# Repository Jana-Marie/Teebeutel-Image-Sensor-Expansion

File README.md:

# Teebeutel Image Sensor Expansion

Upgrade your Teebeutel with different wavelength sensitive parts today!

This addon aims to add minimal thermal vision (GridEye, 8x8px, -20..120°C) to your Teebeutel, as well as an optical camera. However the latter is rather a reverse engineering take on Omnivisions OVM6948 and OV6946 sensors. It also adds a 8x8px ToF camera to your Teebeutel.

Nyaaa~

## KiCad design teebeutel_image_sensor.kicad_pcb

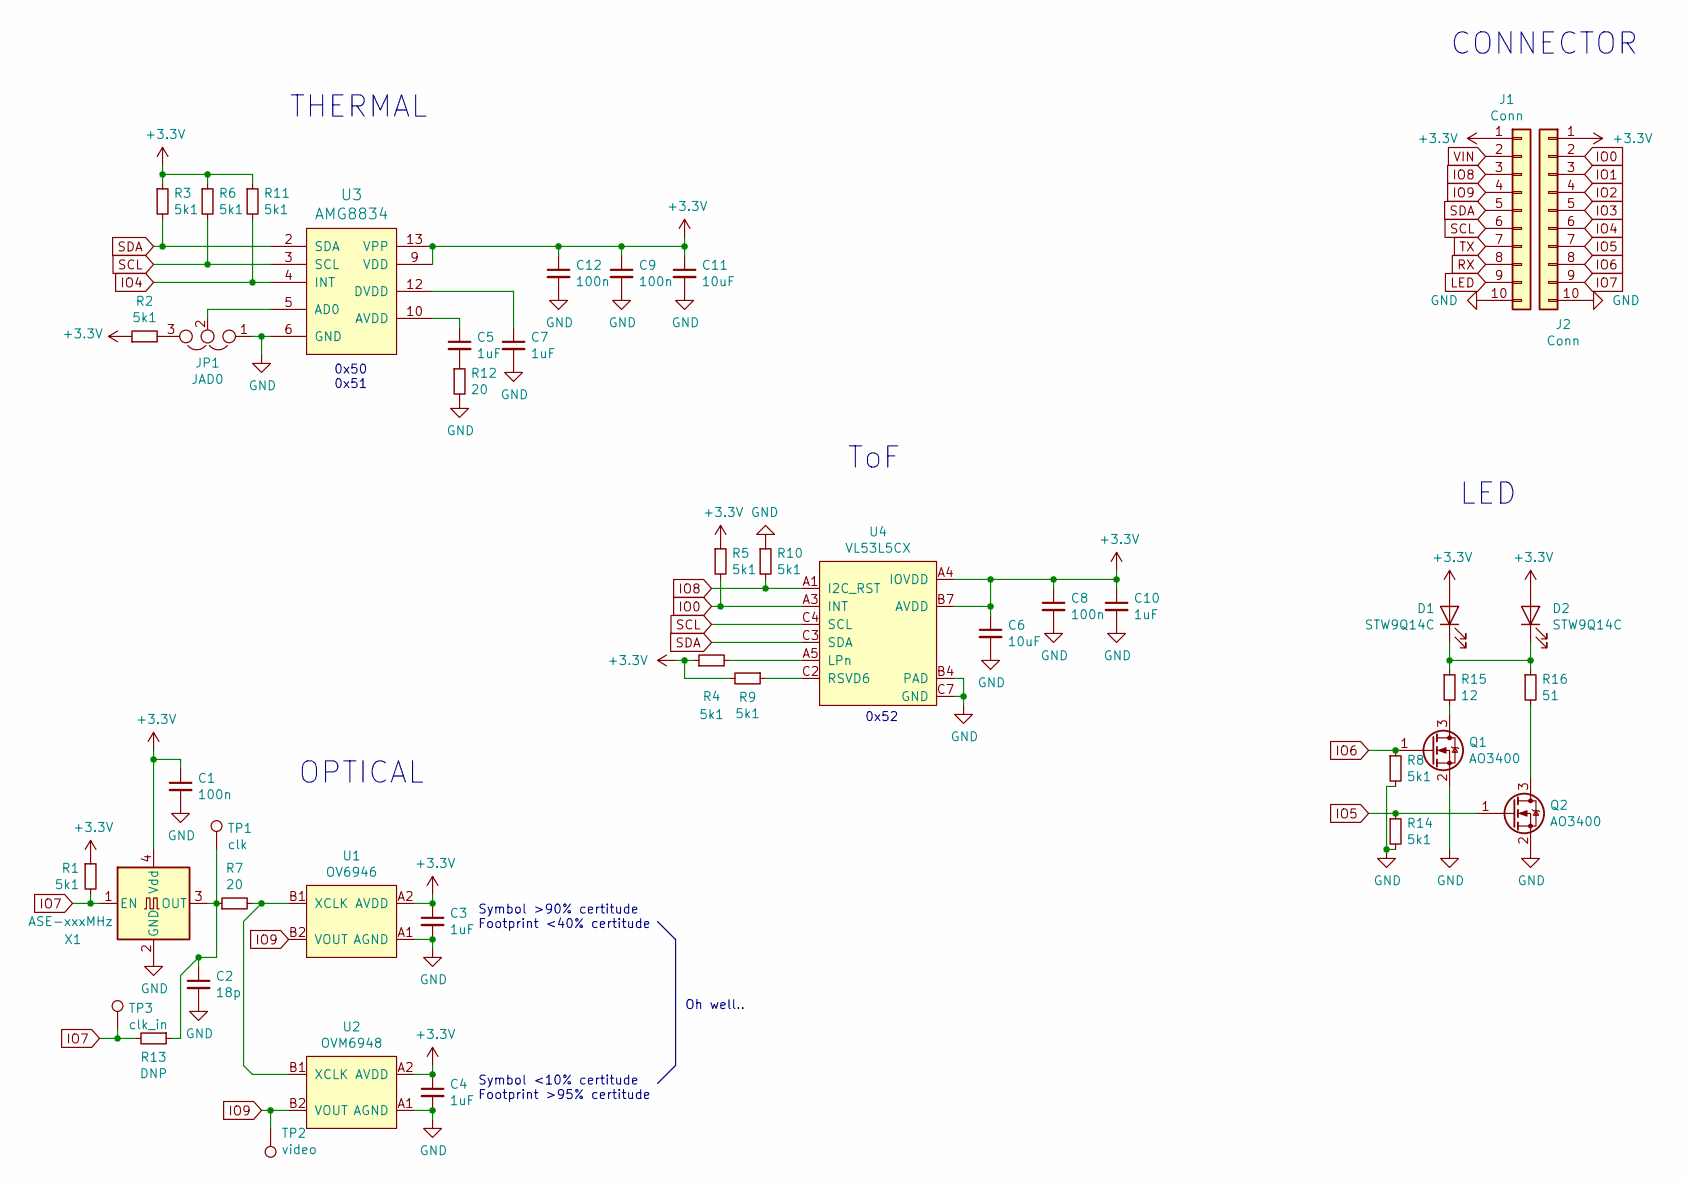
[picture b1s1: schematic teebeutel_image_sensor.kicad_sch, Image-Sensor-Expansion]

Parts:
C1, C8, C9, C12: 100n; C_0402
C2: 18p; C_0402
C3, C4, C5, C7, C10: 1uF; C_0603
C6, C11: 10uF; C_0603
D1, D2: STW9Q14C; 5630
J1, J2: Conn; PinHeader_1x10_P2.54mm_Vertical
JP1: JAD0; J_0402_180
Q1, Q2: AO3400; SOT-23
R1, R2, R3, R4, R5, R6, R8, R9, R10, R11, R14: 5k1; R_0402
R7, R12: 20; R_0402
R13: DNP; R_0402
R15: 12; R_0805
R16: 51; R_0805
TP1: clk; TestPoint_THTPad_1.0x1.0mm_Drill0.5mm
TP2: video; TestPoint_THTPad_1.0x1.0mm_Drill0.5mm
TP3: clk_in; TestPoint_THTPad_1.0x1.0mm_Drill0.5mm
U1: OV6946; OV9646
U2: OVM6948; OVM9648
U3: AMG8834; GridEyeSensor
U4: VL53L5CX; VL53L5
X1: ASE-xxxMHz; Oscillator_SMD_Abracon_ASE-4Pin_3.2x2.5mm

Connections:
+3V3: C1.1, C3.1, C4.1, C6.1, C8.1, C9.1, C10.1, C11.1, C12.1, D1.2 (A), D2.2 (A), J1.1, J2.1, R1.1, R2.1, R3.1, R4.1, R5.1, R6.1, R9.2, R11.1, U1.A2 (AVDD), U2.A2 (AVDD), U3.9 (VDD), U3.13 (VPP), U4.A4 (IOVDD), U4.B1 (AVDD), U4.B7 (AVDD), X1.4 (Vdd)
GND: C1.2, C2.2, C3.2, C4.2, C6.2, C7.2, C8.2, C9.2, C10.2, C11.2, C12.2, J1.10, J2.10, JP1.1, Q1.2 (S), Q2.2 (S), R8.2, R10.1, R12.2, R14.2, U1.A1 (AGND), U2.A1 (AGND), U3.6 (GND), U4.A2 (GND), U4.A6 (GND), U4.A7 (GND), U4.B4 (PAD), U4.C1 (GND), U4.C6 (GND), U4.C7 (GND), X1.2 (GND)
IO0: J2.2, R5.2, U4.A3 (INT)
IO1: J2.3
IO2: J2.4
IO3: J2.5
IO4: J2.6, R11.2, U3.4 (INT)
IO5: J2.7, Q2.1 (G), R14.1
IO6: J2.8, Q1.1 (G), R8.1
IO7: J2.9, R1.2, R13.2, TP3.1, X1.1 (EN)
IO8: J1.3, R10.2, U4.A1 (I2C_RST)
IO9: J1.4, TP2.1, U1.B2 (VOUT), U2.B2 (VOUT)
LED: J1.9
unnamed: C2.1, R7.1, R13.1, TP1.1, X1.3 (OUT)
unnamed: C5.1, U3.10 (AVDD)
unnamed: C5.2, R12.1
unnamed: C7.1, U3.12 (DVDD)
unnamed: D1.1 (K), D2.1 (K), R15.1, R16.1
unnamed: JP1.2, U3.5 (AD0)
unnamed: JP1.3, R2.2
unnamed: Q1.3 (D), R15.2
unnamed: Q2.3 (D), R16.2
unnamed: R4.2, U4.A5 (LPn)
unnamed: R7.2, U1.B1 (XCLK), U2.B1 (XCLK)
unnamed: R9.1, U4.C2 (RSVD6)
RX: J1.8
SCL: J1.6, R6.2, U3.3 (SCL), U4.C4 (SCL)
SDA: J1.5, R3.2, U3.2 (SDA), U4.C3 (SDA)
TX: J1.7
VIN: J1.2

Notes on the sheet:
ToF
0x50 0x51
Symbol <10% certitude Footprint >95% certitude
0x52
Oh well..
THERMAL
OPTICAL
Symbol >90% certitude Footprint <40% certitude
LED
CONNECTOR

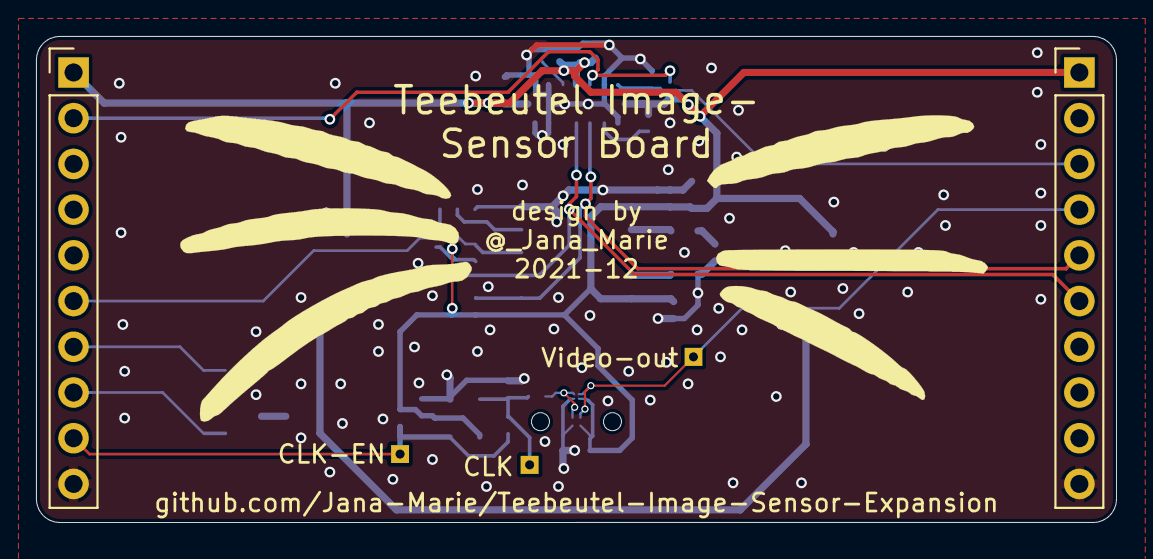
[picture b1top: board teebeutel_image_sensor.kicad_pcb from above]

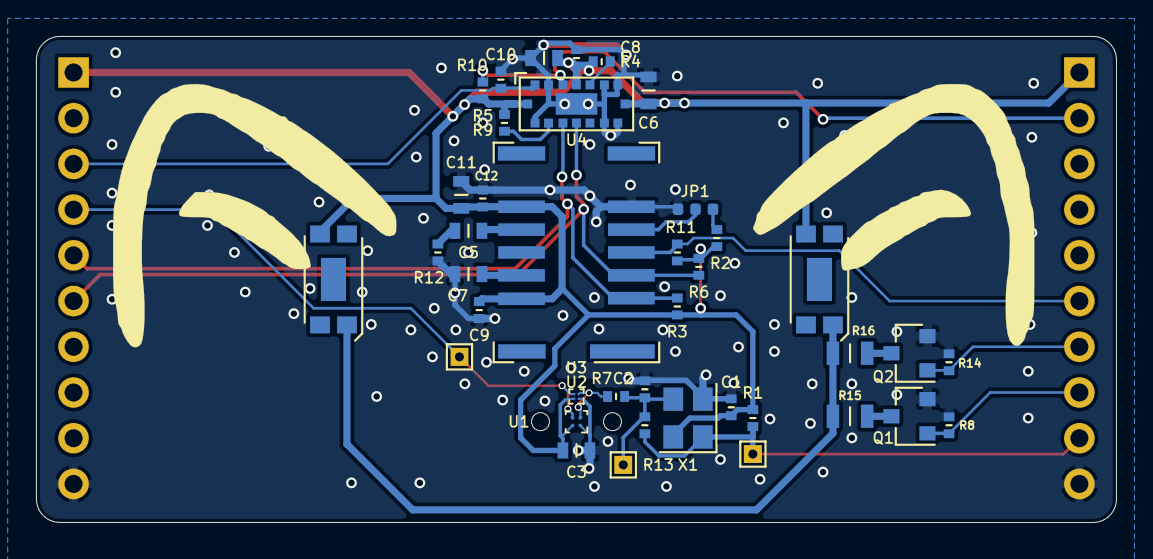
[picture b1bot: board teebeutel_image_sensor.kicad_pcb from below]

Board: 2 copper layers, 60.0 x 27.0 mm, 42 parts (40 on the bottom side), 23 nets.

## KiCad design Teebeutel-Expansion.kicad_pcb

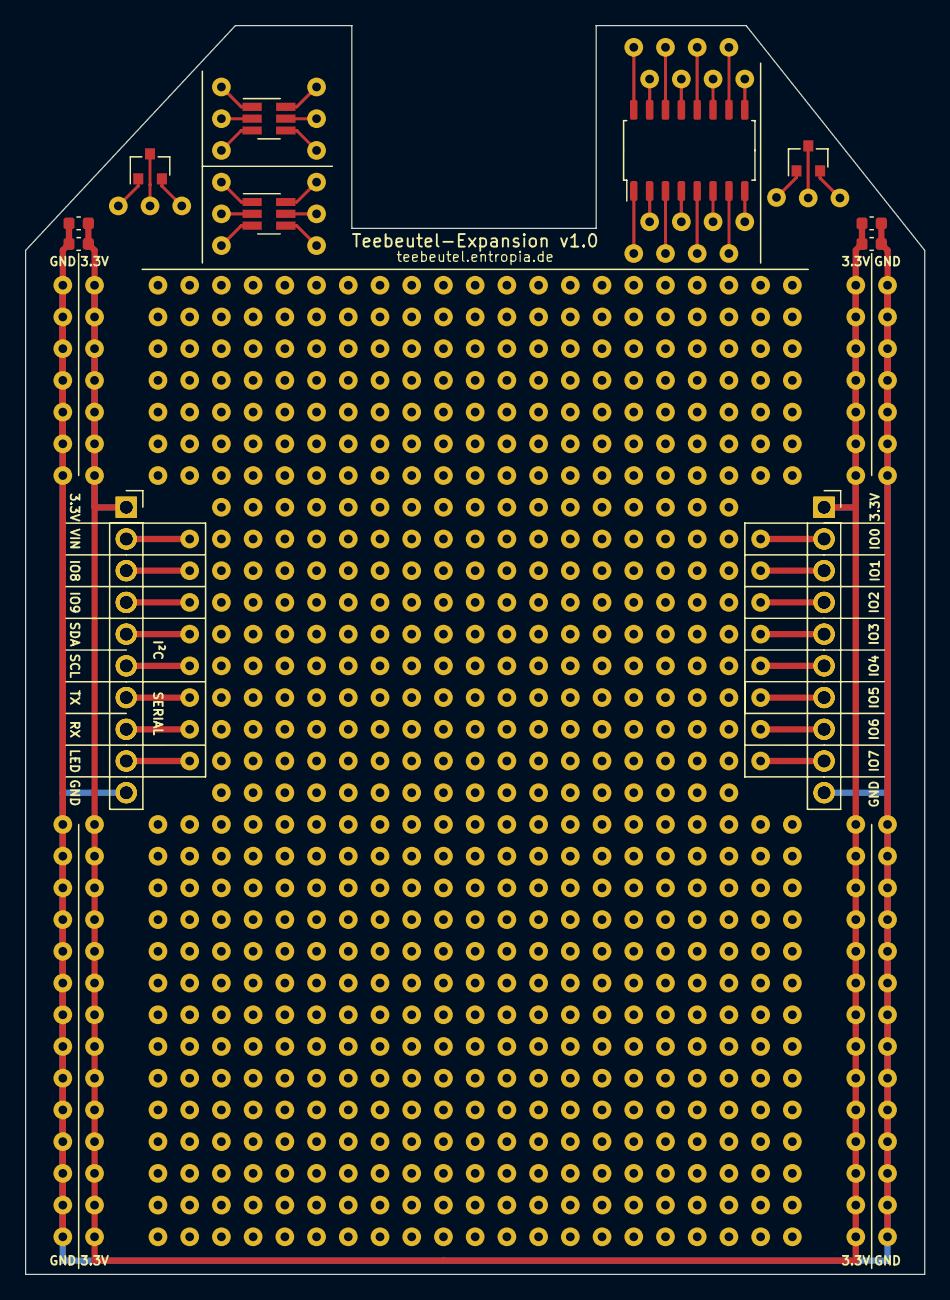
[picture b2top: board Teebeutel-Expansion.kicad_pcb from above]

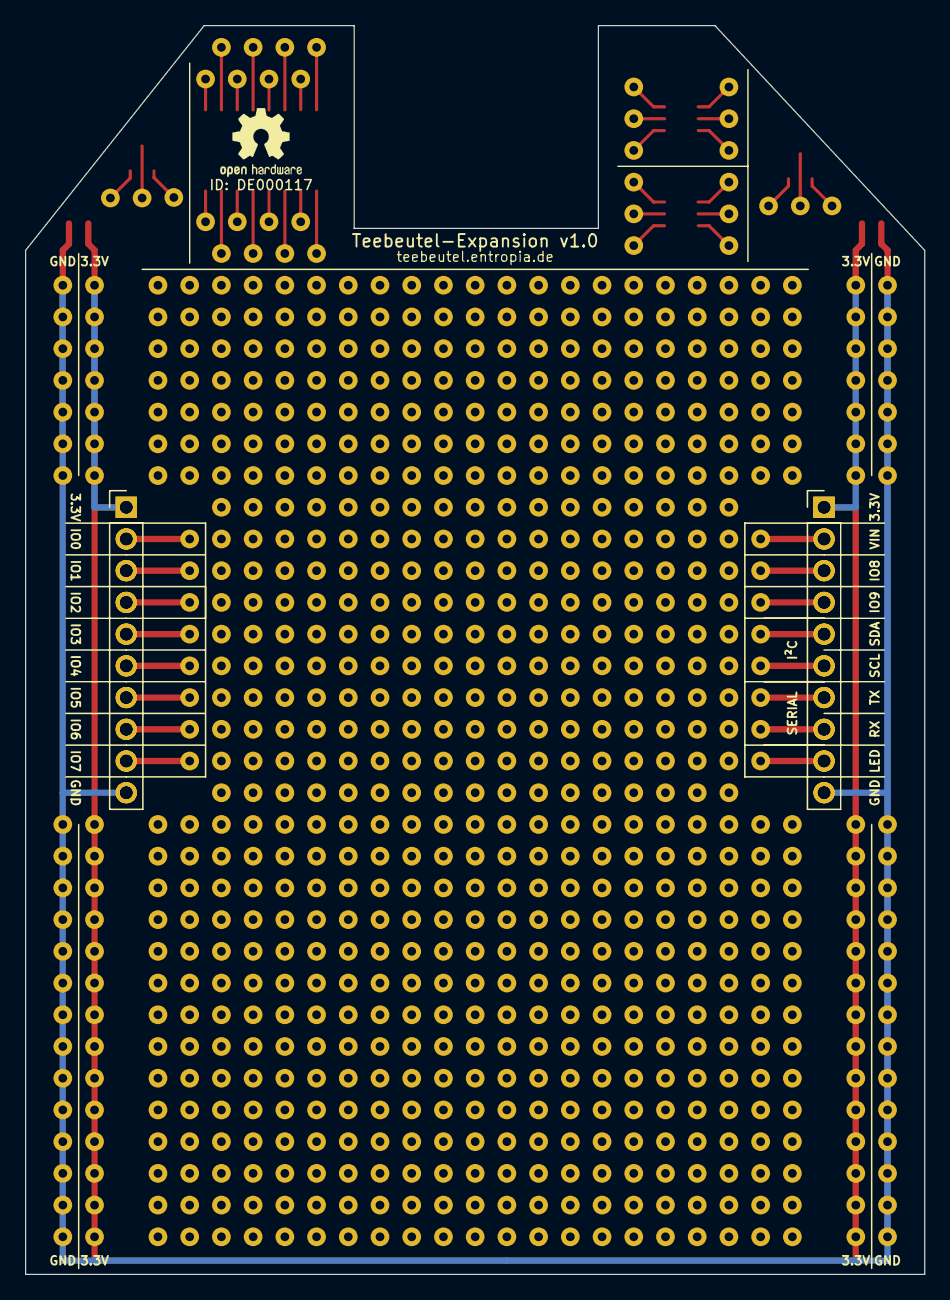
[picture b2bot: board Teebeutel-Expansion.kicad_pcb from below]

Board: 2 copper layers, 72.0 x 100.0 mm, 63 parts (2 on the bottom side), 52 nets.

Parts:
C1, C3: 100nF; C_0603_1608Metric
C2, C4: 10µF; C_0603_1608Metric
J1, J3: Conn_01x10_Male; PinHeader_1x10_P2.54mm_Vertical
J2, J4: Conn_01x10_Female; PinSocket_1x10_P2.54mm_Vertical
J5, J6: Conn_02x03_Counter_Clockwise; SOT-23-6_Handsoldering
J7, J8: Conn_01x03; SOT-23
J9: Conn_02x08_Counter_Clockwise; SOP-16_4.55x10.3mm_P1.27mm
TP1, TP2, TP3, TP4, TP5, TP6, TP7, TP8, TP9, TP10, TP11, TP12, TP13, TP14, TP15, TP16, TP17, TP18, TP19, TP20, TP21, TP22, TP23, TP24, TP25, TP26, TP27, TP28, TP29, TP30, TP31, TP32, TP33, TP34, TP35, TP36, TP37, TP38, TP39, TP40, TP41, TP42, TP43, TP44, TP45, TP46, TP47, TP48, TP49, TP50: TestPoint; THTPad_D1.5mm_Drill0.7mm

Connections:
+3V3: C1.1, C2.1, C3.1, C4.1, J1.1, J2.1, J3.1, J4.1
GND: C1.2, C2.2, C3.2, C4.2, J1.10, J2.10, J3.10, J4.10
I2C-SCL: J1.6, J2.6, TP5.1
I2C-SDA: J1.5, J2.5, TP4.1
IO0: J3.2, J4.2, TP9.1
IO1: J3.3, J4.3, TP10.1
IO2: J3.4, J4.4, TP11.1
IO3: J3.5, J4.5, TP12.1
IO4: J3.6, J4.6, TP13.1
IO5: J3.7, J4.7, TP14.1
IO6: J3.8, J4.8, TP15.1
IO7: J3.9, J4.9, TP16.1
IO8: J1.3, J2.3, TP2.1
IO9: J1.4, J2.4, TP3.1
LED: J1.9, J2.9, TP8.1
unnamed: J5.1, TP17.1
unnamed: J5.2, TP18.1
unnamed: J5.3, TP19.1
unnamed: J5.4, TP25.1
unnamed: J5.5, TP24.1
unnamed: J5.6, TP23.1
unnamed: J6.1, TP20.1
unnamed: J6.2, TP21.1
unnamed: J6.3, TP22.1
unnamed: J6.4, TP28.1
unnamed: J6.5, TP27.1
unnamed: J6.6, TP26.1
unnamed: J7.1, TP29.1
unnamed: J7.2, TP30.1
unnamed: J7.3, TP31.1
unnamed: J8.1, TP32.1
unnamed: J8.2, TP33.1
unnamed: J8.3, TP34.1
unnamed: J9.1, TP35.1
unnamed: J9.2, TP36.1
unnamed: J9.3, TP37.1
unnamed: J9.4, TP38.1
unnamed: J9.5, TP39.1
unnamed: J9.6, TP40.1
unnamed: J9.7, TP41.1
unnamed: J9.8, TP42.1
unnamed: J9.9, TP50.1
unnamed: J9.10, TP49.1
unnamed: J9.11, TP48.1
unnamed: J9.12, TP47.1
unnamed: J9.13, TP46.1
unnamed: J9.14, TP45.1
unnamed: J9.15, TP44.1
unnamed: J9.16, TP43.1
RxD: J1.8, J2.8, TP7.1
TxD: J1.7, J2.7, TP6.1
VIN: J1.2, J2.2, TP1.1

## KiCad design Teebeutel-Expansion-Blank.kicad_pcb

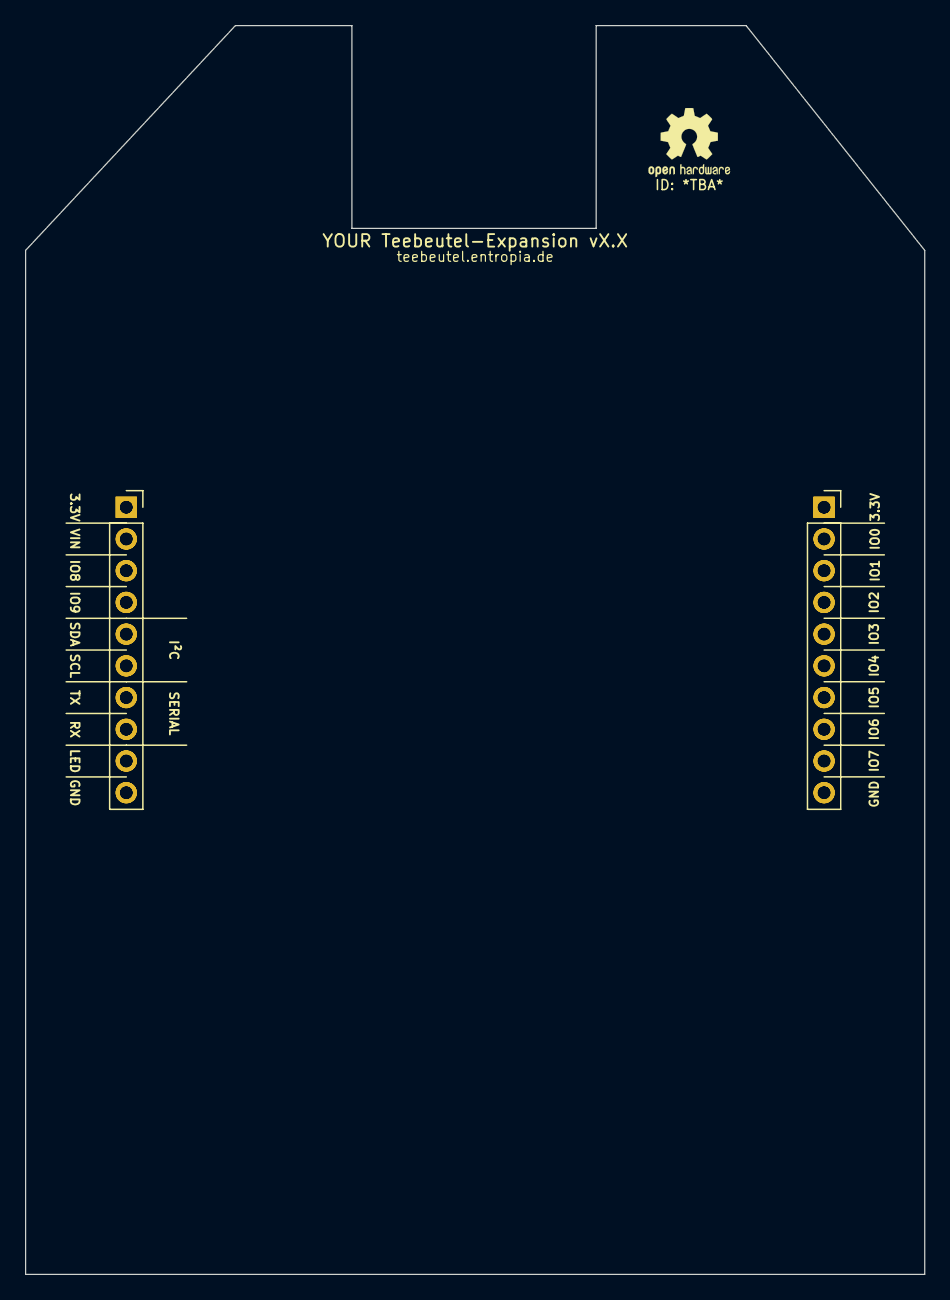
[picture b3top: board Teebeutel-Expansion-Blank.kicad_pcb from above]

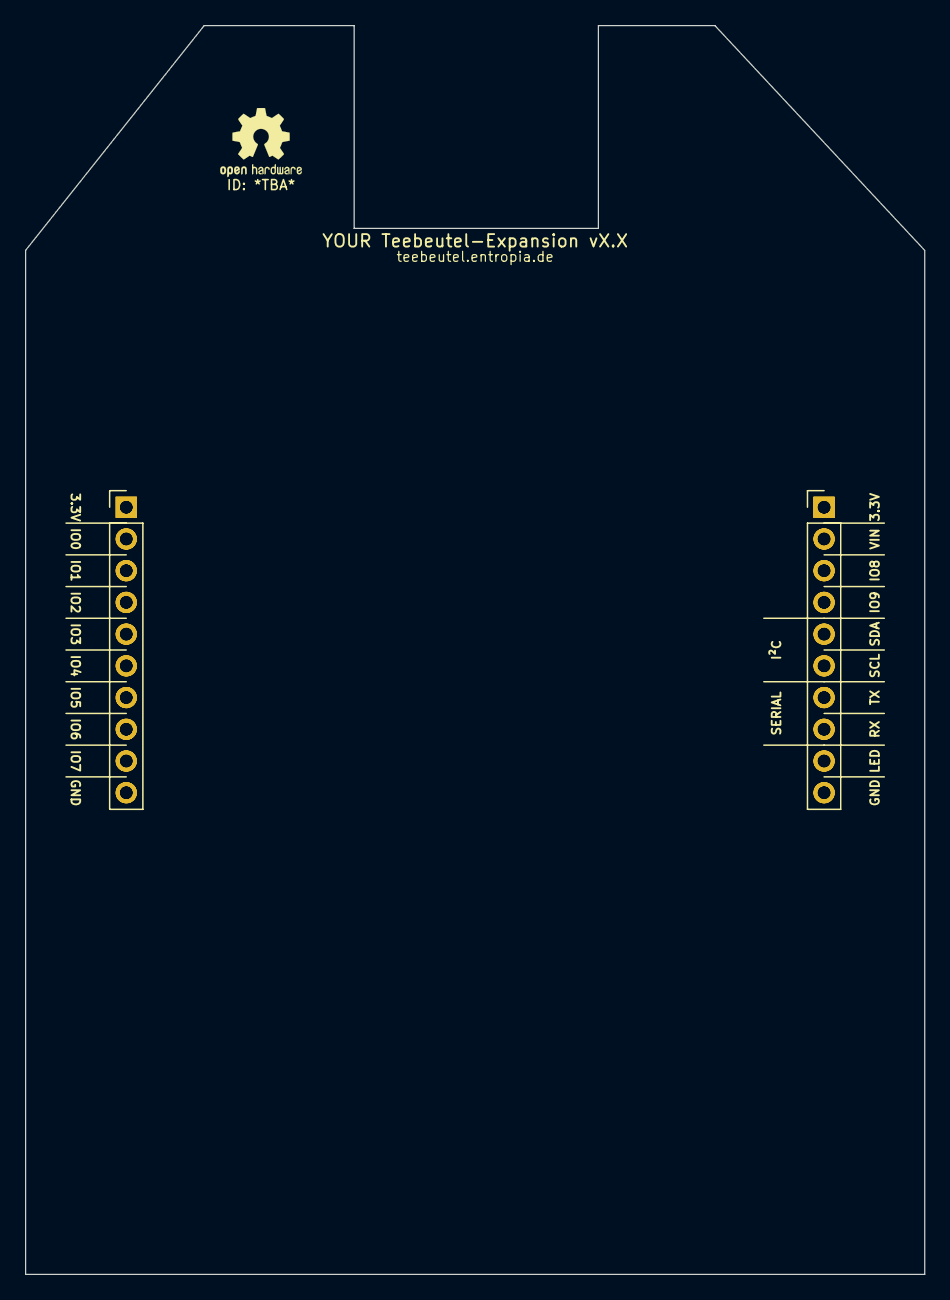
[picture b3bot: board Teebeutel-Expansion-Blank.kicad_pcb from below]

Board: 2 copper layers, 72.0 x 100.0 mm, 4 parts (2 on the bottom side), 18 nets, no tracks yet.

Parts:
J1, J3: Conn_01x10_Male; PinHeader_1x10_P2.54mm_Vertical
J2, J4: Conn_01x10_Female; PinSocket_1x10_P2.54mm_Vertical

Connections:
+3V3: J1.1, J2.1, J3.1, J4.1
GND: J1.10, J2.10, J3.10, J4.10
I2C-SCL: J1.6, J2.6
I2C-SDA: J1.5, J2.5
IO0: J3.2, J4.2
IO1: J3.3, J4.3
IO2: J3.4, J4.4
IO3: J3.5, J4.5
IO4: J3.6, J4.6
IO5: J3.7, J4.7
IO6: J3.8, J4.8
IO7: J3.9, J4.9
IO8: J1.3, J2.3
IO9: J1.4, J2.4
LED: J1.9, J2.9
RxD: J1.8, J2.8
TxD: J1.7, J2.7
VIN: J1.2, J2.2

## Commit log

2021-12-24 removed blank files
2021-12-24 renamed files
2021-12-24 added gerber
2021-12-24 added renderings
2021-12-29 added new images
2022-01-03 moved to kicad 6, generated gerber

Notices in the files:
Teebeutel-Expansion-Blank.kicad_pcb:
License: CERN-OHL-S
Please remember to publish your Expansion under an OSHW-License!
